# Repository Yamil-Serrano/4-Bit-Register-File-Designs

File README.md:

# 4-Bit Register File Designs

A collection of 4-bit register file implementations
exploring architectural trade-offs between
hardware minimalism and full register flexibility.
These designs demonstrate how storage, decoding,
and multiplexing interact inside a CPU register file
using discrete logic ICs and explicit wiring.

This repository includes two complete register file
architectures: a minimalist split-read design using
74HC157 multiplexers, and a fully flexible design
using 74HC153 multiplexers. Together, they show how
architectural decisions directly affect hardware
complexity, wiring density, and instruction freedom.

# Minimalist 4-Bit Register File (RB1574B – Split Read Architecture)

RB1574B represents a hardware-minimalist approach
to register file design. It is built entirely
from discrete logic ICs and focuses on reducing
the number of multiplexers required for register
selection while maintaining full write capability.

The architecture uses a split read model, where
each read port accesses a different subset of
registers. This limits some register-to-register
operations but significantly reduces hardware
complexity and control logic.

## Technical Specifications

### Core Features

* **Register Count**: 4 general-purpose registers
* **Register Width**: 4-bit parallel storage
* **Storage Type**: Edge-triggered D-type flip-flops
* **Read Ports**:

  * RS1: Register 1 or Register 2
  * RS2: Register 3 or Register 4
* **Write Port**: Single global RegWrite signal
* **Clocked Write**: Yes

## Integrated Circuits Used

| IC          | Function              | Quantity | Purpose                 |
| ----------- | --------------------- | -------- | ----------------------- |
| **74HC173** | 4-bit D-type Register | 4        | Register storage        |
| **74HC157** | 2:1 Multiplexer       | 2        | Read path selection     |
| **74HC238** | 3-to-8 Decoder        | 1        | Register write decoding |
| **74HC00**  | Quad NAND Gate        | 1        | RegWrite gating logic   |

## Hardware Implementation

### Circuit Design

## Architecture Details

### Read Operation

* RS1 selects between Register 1 and Register 2
* RS2 selects between Register 3 and Register 4
* Registers within the same group cannot be read together
* Cross-group operations are supported

This split read structure mirrors constrained or
early CPU designs where hardware limitations
shape instruction-level flexibility.

### Write Operation

* A 74HC238 decoder selects one register
* NAND gates combine decoder outputs with RegWrite
* Only the selected register is enabled for writing
* Write access is fully flexible across all registers

### Breadboard Implementation

## Design Philosophy

RB1574B prioritizes simplicity and hardware efficiency.
By limiting read flexibility, the design reduces
chip count, wiring density, and control complexity.
This architecture demonstrates how physical hardware
constraints directly influence CPU behavior.

## Known Limitations

1. Not all register-to-register combinations are possible
2. RS1 and RS2 access disjoint register groups
3. Additional data movement instructions may be required

# Full 4-Bit Register File (RB1534B – Complete Read Architecture)

RB1534B represents a fully flexible register file implementation. Both read ports can independently access any register, enabling all possible register-to-register operations in hardware. This completeness comes at the cost of increased multiplexing logic, dense wiring, and higher visual complexity, especially in discrete IC designs.

### Core Features

- **Register Count**: 4 general-purpose registers
- **Register Width**: 4-bit parallel storage
- **Storage Type**: Edge-triggered D-type flip-flops
- **Read Ports**: Two fully independent read outputs
- **Write Port**: Single global RegWrite signal
- **Clocked Write**: Yes

### Integrated Circuits Used

| IC | Function | Quantity | Purpose |
| --- | --- | --- | --- |
| **74HC173** | 4-bit D-type Register | 4 | Register storage |
| **74HC153** | Dual 4:1 Multiplexer | 4 | Full read selection |
| **74HC238** | 3-to-8 Decoder | 1 | Register write decoding |
| **74HC00** | Quad NAND Gate | 1 | RegWrite gating logic |

**Total Components**: 10 ICs, implementing a complete 4-bit register file with full read/write flexibility.

## Hardware Implementation

### Circuit Design

### PCB Design in KiCad

After validating the architecture in simulation, the design was migrated from breadboard to a custom PCB manufactured via JLCPCB. Each IC is paired with a dedicated 100nF ceramic bypass capacitor placed directly at the power pins to suppress switching noise. A 100µF bulk electrolytic capacitor stabilizes the 5V supply rail.

### Physical Build

## Verification & Test Bench

To validate correct operation across all possible register file states, a dedicated test bench was developed using an ESP32 microcontroller. The [`firmware`](./src/tester/src) exhaustively tests all register read/write combinations. Due to I/O pin limitations on the ESP32, the two read ports (RS1 and RS2) could not be tested simultaneously. Instead, a sequential verification strategy was employed:

- **RS1 Validation**: First, all register read/write combinations were exhaustively tested using Read Port 1 (RS1). Every possible write pattern (0–15) was written to each of the 4 registers, and RS1 independently selected each register to verify output correctness.
- **RS2 Validation**: After confirming 100% correct operation of RS1, the same test harness was reconfigured (pins reassigned) to validate Read Port 2 (RS2) identically.
- **Write Verification**: Writes a unique 4-bit pattern (0–15) to each of the 4 registers across multiple cycles.
- **Independence Test**: Verifies that writing to one register does not affect the contents of other registers.
- **RegWrite Gating**: Ensures that when RegWrite is low, no register state changes occur.

A total of 2,048 possible register file states (4 registers × 16 values × 16 read combinations for each port) were tested per read port, with both ports passing with 100% accuracy. Results are reported over Serial with ANSI color coding, distinguishing passing tests in green from failures in red. A 20×4 LCD display connected via I2C provides a real-time progress bar during testing and a summary screen upon completion.

### Operation Details

#### 1. **Register Write Operation**

- Write address decoded via 74HC238 3-to-8 decoder
- RegWrite signal gated with clock edge using 74HC00 NAND logic
- Data applied to all 74HC173 registers, but only selected register accepts new value on clock edge

#### 2. **Register Read Operation – Port 1 (RS1)**

- 2× 74HC153 multiplexers select any of the 4 registers
- 2-bit RS1 address selects which register appears on Read Data 1 bus

#### 3. **Register Read Operation – Port 2 (RS2)**

- Independent 2× 74HC153 multiplexer bank (separate from RS1)
- 2-bit RS2 address selects any register for Read Data 2 bus
- Both read ports operate simultaneously with zero contention

## Design Philosophy

RB1534B prioritizes architectural completeness over hardware simplicity. Every register selection is explicitly decoded and multiplexed, making this design ideal for studying scalable CPU register files and data-path construction.

## Comparative Summary

| Feature | RB1574B | RB1534B |
| --- | --- | --- |
| Read Flexibility | Limited (2×2) | Full (4×4) |
| Write Flexibility | Full | Full |
| Chip Count | Low | High |
| Wiring Density | Low | Very High |
| Educational Focus | Constraints | Completeness |

# FPGA Implementation: 4-Bit Register File (Tang Nano 9K)

This module implements a 4-bit register file on the Sipeed Tang Nano 9K FPGA, translating a discrete, flip-flop–based register file into a compact HDL description. The design faithfully recreates a classic hardware register file built from D flip-flops, a 2-to-4 decoder, and external multiplexers, preserving the original architectural intent while leveraging FPGA integration. The register file serves as a foundational storage element for a CPU-style datapath, providing controlled write access and multiple read paths suitable for ALU operand sourcing.

## Physical Prototype & Interfacing

To maintain a hands-on and educational workflow, the FPGA is interfaced with external switches and LEDs, closely mirroring the behavior and observability of the original discrete implementation.

**Input (Switches):**

* A 4-bit switch group provides *speculative ALU data*, allowing manual injection of values into the register file.
* Additional switches select the write register address and control the global write enable (`RegWrite`).
* All inputs use pull-down configurations to guarantee stable logic levels and avoid floating inputs.

**Output (LEDs):**

* Two independent 4-bit LED groups display the contents of the selected source registers (`rs1` and `rs2`).
* LEDs operate in an active-high configuration, where illumination represents a logic high (`1`).

This interface allows direct visual confirmation of register contents and write/read behavior in real time.

*Tang Nano 9K demonstrating manual register writes and LED-based readout.*

## Design Philosophy & Notes

* **Discrete-to-HDL Fidelity**: The register file was intentionally described using explicit registers, a decoder, and multiplexers to mirror the original TTL-based design (e.g., 74HC238 for decoding and 74HC157 for selection), rather than relying on abstract HDL shortcuts.
* **Educational Transparency**: Each register is represented explicitly, making the data flow and control logic easy to trace and reason about, especially for learners transitioning from breadboard-based designs to HDL.
* **Controlled Write Semantics**: A global write enable combined with a decoded register select ensures that exactly one register captures data on a rising clock edge, replicating real-world register file behavior.
* **Modular Expansion**: Exposing individual register outputs enables flexible experimentation, such as external multiplexing, debugging, or future ALU integration.

## Comparative Summary: Discrete vs. FPGA Register File

| Aspect               | Discrete IC Implementation                          | FPGA Implementation                                      |
| :------------------- | :-------------------------------------------------- | :------------------------------------------------------- |
| **Component Count**  | Multiple flip-flops, decoder, and multiplexers.     | **1** FPGA device.                                       |
| **Storage Elements** | Individual 74HC173 wired by hand.                   | Synthesized registers from HDL.                          |
| **Address Decoding** | Physical 74HC238 decoder IC.                        | Behavioral decoder logic.                                |
| **Read Selection**   | External multiplexers (e.g., 74HC157).              | Combinational HDL multiplexing.                          |
| **Flexibility**      | Fixed wiring; modifications require rewiring.       | **Reconfigurable** via HDL changes.                      |
| **Learning Focus**   | Understanding register-level hardware construction. | Bridging discrete logic concepts into FPGA-based design. |

### Historical Note:

While working on this design, I later discovered the 74HC670, a single IC that could implement a full 4-bit register file with all read/write flexibility. At that point, I had already spent around $35 on multiple ICs (157s, 153s, 173s, etc.) to build the RB157 and RB153 designs, while the 74HC670 costs around $10. However, building the register files with discrete components first gave me deep insight into MUX cascading, RegWrite logic, and architectural limitations.

Reflection: If I had bought the 74HC670 from the start:

* I would not have understood MUX cascades
* I would not have understood RegWrite
* I would not have seen real limitations
* The chip would have been a black box

With $10 you could buy a fully functional chip. With $35, you bought deep understanding and hands-on experience.

## License

Licensed under the **Solderpad Hardware License v2.1**.
See the [LICENSE](LICENSE-HARDWARE) file for full terms.

## Contact

If you have any questions or suggestions, feel free to reach out:

* **GitHub:** [Neowizen](https://github.com/Yamil-Serrano)

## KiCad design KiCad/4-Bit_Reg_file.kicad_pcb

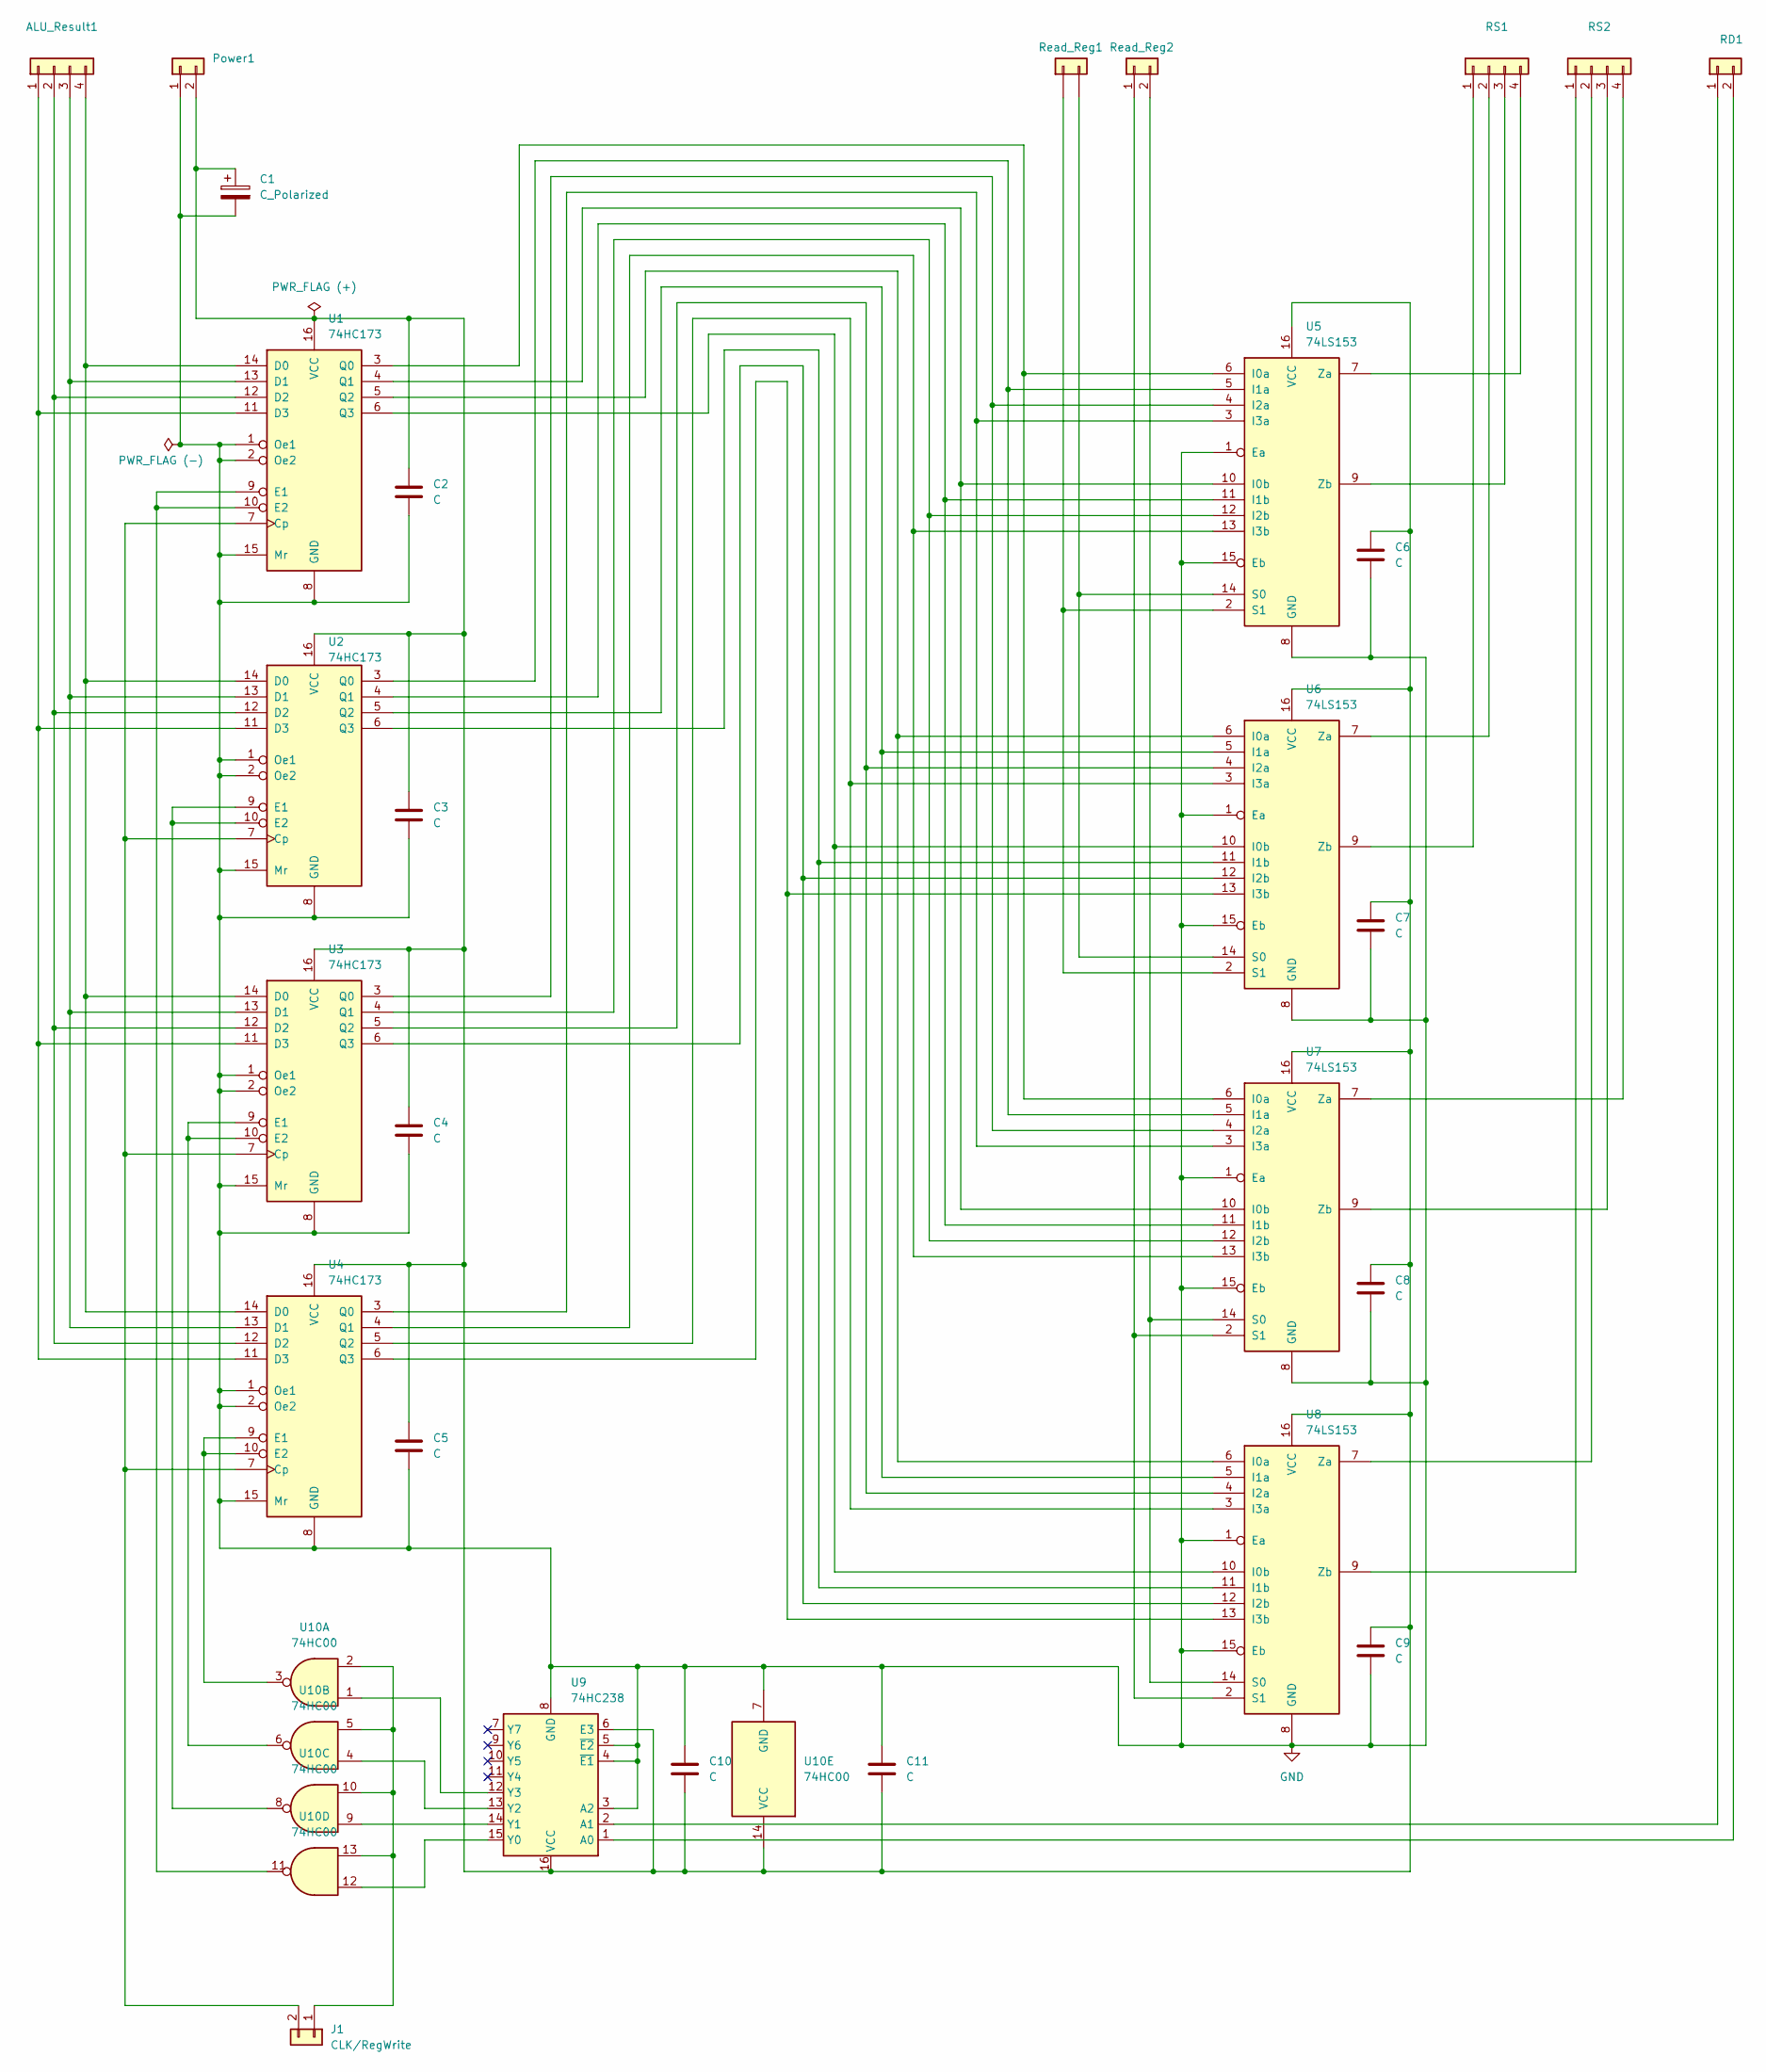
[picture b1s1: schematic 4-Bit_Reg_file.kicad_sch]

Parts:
ALU_Result1: Conn_01x04; PinHeader_1x04_P2.54mm_Vertical
C1: C_Polarized; CP_Radial_D4.0mm_P1.50mm
C2, C3, C4, C5, C6, C7, C8, C9, C10, C11: C; C_Disc_D3.0mm_W1.6mm_P2.50mm
J1: CLK/RegWrite; PinHeader_1x02_P2.54mm_Vertical
Power1: Conn_01x02; PinHeader_1x02_P2.54mm_Vertical
RD1: Conn_01x02; PinHeader_1x02_P2.54mm_Vertical
RS1, RS2: Conn_01x04; PinHeader_1x04_P2.54mm_Vertical
Read_Reg1, Read_Reg2: Conn_01x02; PinHeader_1x02_P2.54mm_Vertical
U1, U2, U3, U4: 74HC173; DIP-16_W7.62mm_Socket
U5, U6, U7, U8: 74LS153; DIP-16_W7.62mm_Socket
U9: 74HC238; DIP-16_W7.62mm_Socket
U10: 74HC00; DIP-14_W7.62mm_Socket

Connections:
GND: C1.2, C2.2, C3.2, C4.2, C5.2, C6.2, C7.2, C8.2, C9.2, C10.1, C11.1, Power1.1, U1.1 (Oe1), U1.2 (Oe2), U1.8 (GND), U1.15 (Mr), U2.1 (Oe1), U2.2 (Oe2), U2.8 (GND), U2.15 (Mr), U3.1 (Oe1), U3.2 (Oe2), U3.8 (GND), U3.15 (Mr), U4.1 (Oe1), U4.2 (Oe2), U4.8 (GND), U4.15 (Mr), U5.1 (Ea), U5.8 (GND), U5.15 (Eb), U6.1 (Ea), U6.8 (GND), U6.15 (Eb), U7.1 (Ea), U7.8 (GND), U7.15 (Eb), U8.1 (Ea), U8.8 (GND), U8.15 (Eb), U9.3 (A2), U9.4 (~E1), U9.5 (~E2), U9.8 (GND), U10.7 (GND)
unnamed: ALU_Result1.1, U1.11 (D3), U2.11 (D3), U3.11 (D3), U4.11 (D3)
unnamed: ALU_Result1.2, U1.12 (D2), U2.12 (D2), U3.12 (D2), U4.12 (D2)
unnamed: ALU_Result1.3, U1.13 (D1), U2.13 (D1), U3.13 (D1), U4.13 (D1)
unnamed: ALU_Result1.4, U1.14 (D0), U2.14 (D0), U3.14 (D0), U4.14 (D0)
unnamed: J1.1, U10.2, U10.5, U10.10, U10.13
unnamed: J1.2, U1.7 (Cp), U2.7 (Cp), U3.7 (Cp), U4.7 (Cp)
unnamed: C1.1, C2.1, C3.1, C4.1, C5.1, C6.1, C7.1, C8.1, C9.1, C10.2, C11.2, Power1.2, U1.16 (VCC), U2.16 (VCC), U3.16 (VCC), U4.16 (VCC), U5.16 (VCC), U6.16 (VCC), U7.16 (VCC), U8.16 (VCC), U9.6 (E3), U9.16 (VCC), U10.14 (VCC)
unnamed: RD1.1, U9.2 (A1)
unnamed: RD1.2, U9.1 (A0)
unnamed: RS1.1, U6.9 (Zb)
unnamed: RS1.2, U6.7 (Za)
unnamed: RS1.3, U5.9 (Zb)
unnamed: RS1.4, U5.7 (Za)
unnamed: RS2.1, U8.9 (Zb)
unnamed: RS2.2, U8.7 (Za)
unnamed: RS2.3, U7.9 (Zb)
unnamed: RS2.4, U7.7 (Za)
unnamed: Read_Reg1.1, U5.2 (S1), U6.2 (S1)
unnamed: Read_Reg1.2, U5.14 (S0), U6.14 (S0)
unnamed: Read_Reg2.1, U7.2 (S1), U8.2 (S1)
unnamed: Read_Reg2.2, U7.14 (S0), U8.14 (S0)
unnamed: U1.9 (E1), U1.10 (E2), U10.11
unnamed: U1.3 (Q0), U5.6 (I0a), U7.6 (I0a)
unnamed: U1.4 (Q1), U5.10 (I0b), U7.10 (I0b)
unnamed: U1.5 (Q2), U6.6 (I0a), U8.6 (I0a)
unnamed: U1.6 (Q3), U6.10 (I0b), U8.10 (I0b)
unnamed: U2.9 (E1), U2.10 (E2), U10.8
unnamed: U2.3 (Q0), U5.5 (I1a), U7.5 (I1a)
unnamed: U2.4 (Q1), U5.11 (I1b), U7.11 (I1b)
unnamed: U2.5 (Q2), U6.5 (I1a), U8.5 (I1a)
unnamed: U2.6 (Q3), U6.11 (I1b), U8.11 (I1b)
unnamed: U3.9 (E1), U3.10 (E2), U10.6
unnamed: U3.3 (Q0), U5.4 (I2a), U7.4 (I2a)
unnamed: U3.4 (Q1), U5.12 (I2b), U7.12 (I2b)
unnamed: U3.5 (Q2), U6.4 (I2a), U8.4 (I2a)
unnamed: U3.6 (Q3), U6.12 (I2b), U8.12 (I2b)
unnamed: U4.9 (E1), U4.10 (E2), U10.3
unnamed: U4.3 (Q0), U5.3 (I3a), U7.3 (I3a)
unnamed: U4.4 (Q1), U5.13 (I3b), U7.13 (I3b)
unnamed: U4.5 (Q2), U6.3 (I3a), U8.3 (I3a)
unnamed: U4.6 (Q3), U6.13 (I3b), U8.13 (I3b)
unnamed: U9.15 (Y0), U10.12
unnamed: U9.14 (Y1), U10.9
unnamed: U9.13 (Y2), U10.4
unnamed: U9.12 (Y3), U10.1

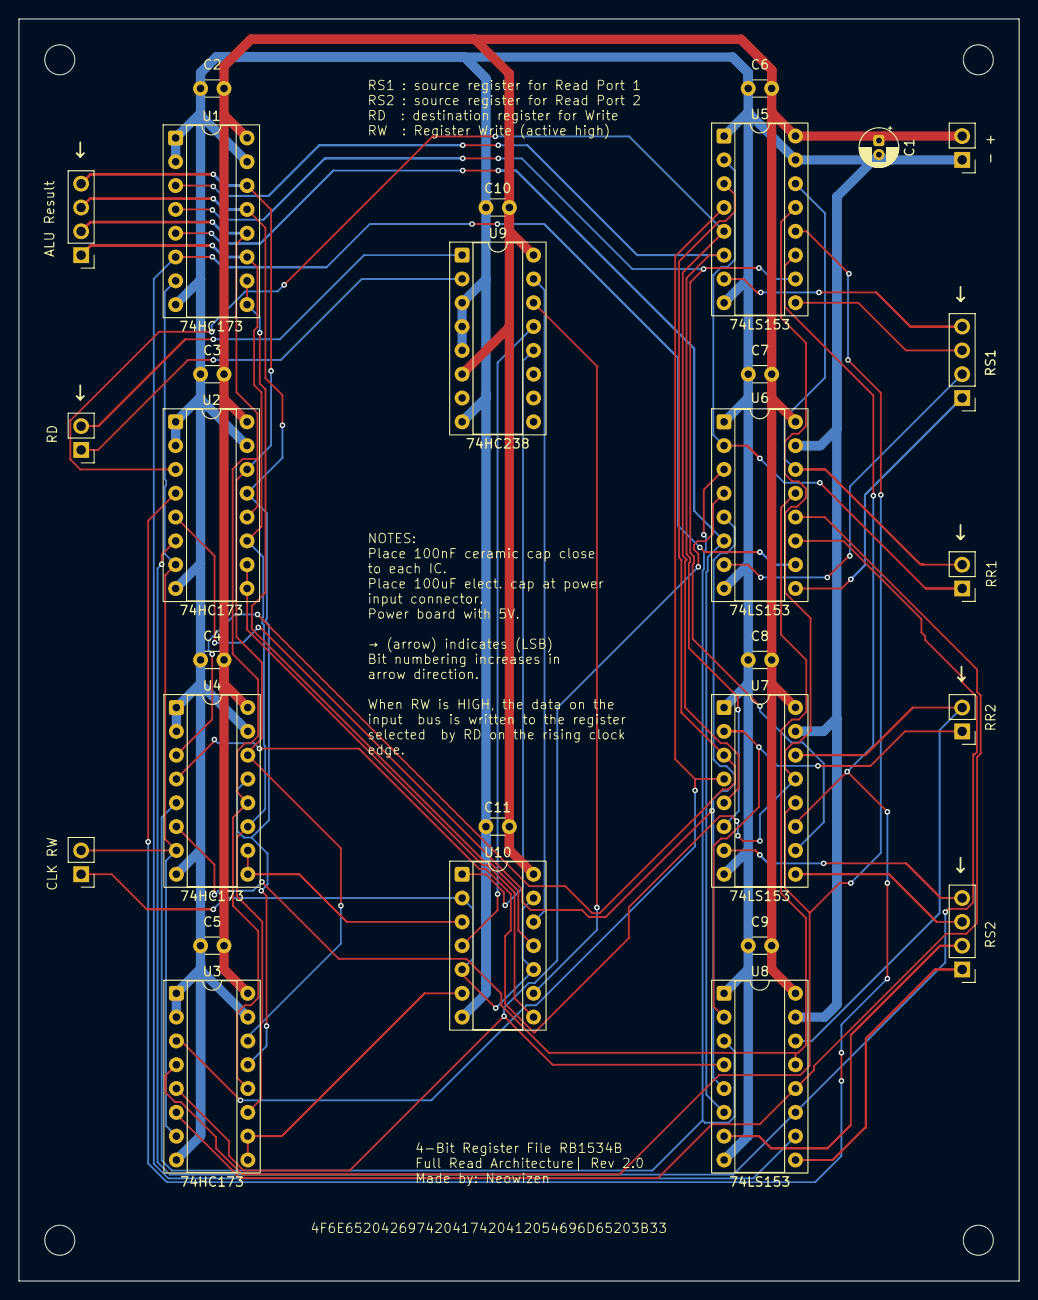
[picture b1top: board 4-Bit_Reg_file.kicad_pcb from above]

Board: 2 copper layers, 106.7 x 134.6 mm, 29 parts (0 on the bottom side), 46 nets.

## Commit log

2025-12-18 Enhance README with detailed design documentation
    Updated README to provide detailed descriptions of the 4-bit register bank designs, including technical specifications, architecture details, and comparative summaries.
2025-12-21 Add Solderpad Hardware License v2.1
2025-12-21 Update README with license and contact details
    Added license and contact information sections.
2025-12-23 Add Verilog files via upload
2025-12-23 Revise README for terminology and FPGA details
    Updated terminology from 'register bank' to 'register file' throughout the README. Added FPGA implementation details and comparative summaries between discrete and FPGA designs.
2025-12-31 Add Breadboard Implementation section to README
    Added a section on Breadboard Implementation with an image.
2026-01-07 Replace circuit design images with new versions
    Updated circuit design images in the README.
2026-05-21 Update circuit image and modify write operation details
    Updated image in Circuit Design section and removed a line in Write Operation section.
2026-06-07 Add 4-Bit Register File tester firmware and configuration files
2026-06-07 Revise README for clarity and structure
    Updated README to improve clarity and organization of content, including circuit design images and detailed architecture descriptions.
2026-06-07 Add 4-Bit Reg file KiCad project
2026-06-14 Title block added to schematic
